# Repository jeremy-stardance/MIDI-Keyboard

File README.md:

## MIDI Keyboard Project

This is for week 3 of Hack Club Half-Life

This is my schematic for eight buttons, run on an Arduino Pro Micro. It should allow me to create an output of notes C through to C.

Here is the PCB design. The wiring is very satisfying.

## Bill Of Materials

| Component | Quantity | Cost ($) |
|---|---:|---:|
| Arduino Pro Micro | 1 | 9.33 |
| Breadboard | 1 | 8.85 |
| Jumper Wire | 130 | 7.92 |

The prices are in $USD. I am using the Arduino Pro Micro as a 'brain' for the project. The wires will be used to jump across my PCB Development Board, and I will use the breadboard to test code and wiring because I am not confident enough in my code to want to just hope for the best.

I already own a PCB Development Board, and 8 Buttons, so didn't need to but them on the BOM.

## What I Have Learnt

Before this, I had only used arduino templates as code, but this is the first time I actually tweaked and changed code. I had to learn a little bit of the coding language (with help from AI). 

Also, I had to learn to find my own schematic files and footprints, rather than have them given to me like in the Starbie project using the tutorial. This took some time.

## Why a MIDI Keyboard

I play piano as a hobby. I thought that a MIDI Keyboard would be a cool devise to be able to have, even though it will not have any sharps or flats.

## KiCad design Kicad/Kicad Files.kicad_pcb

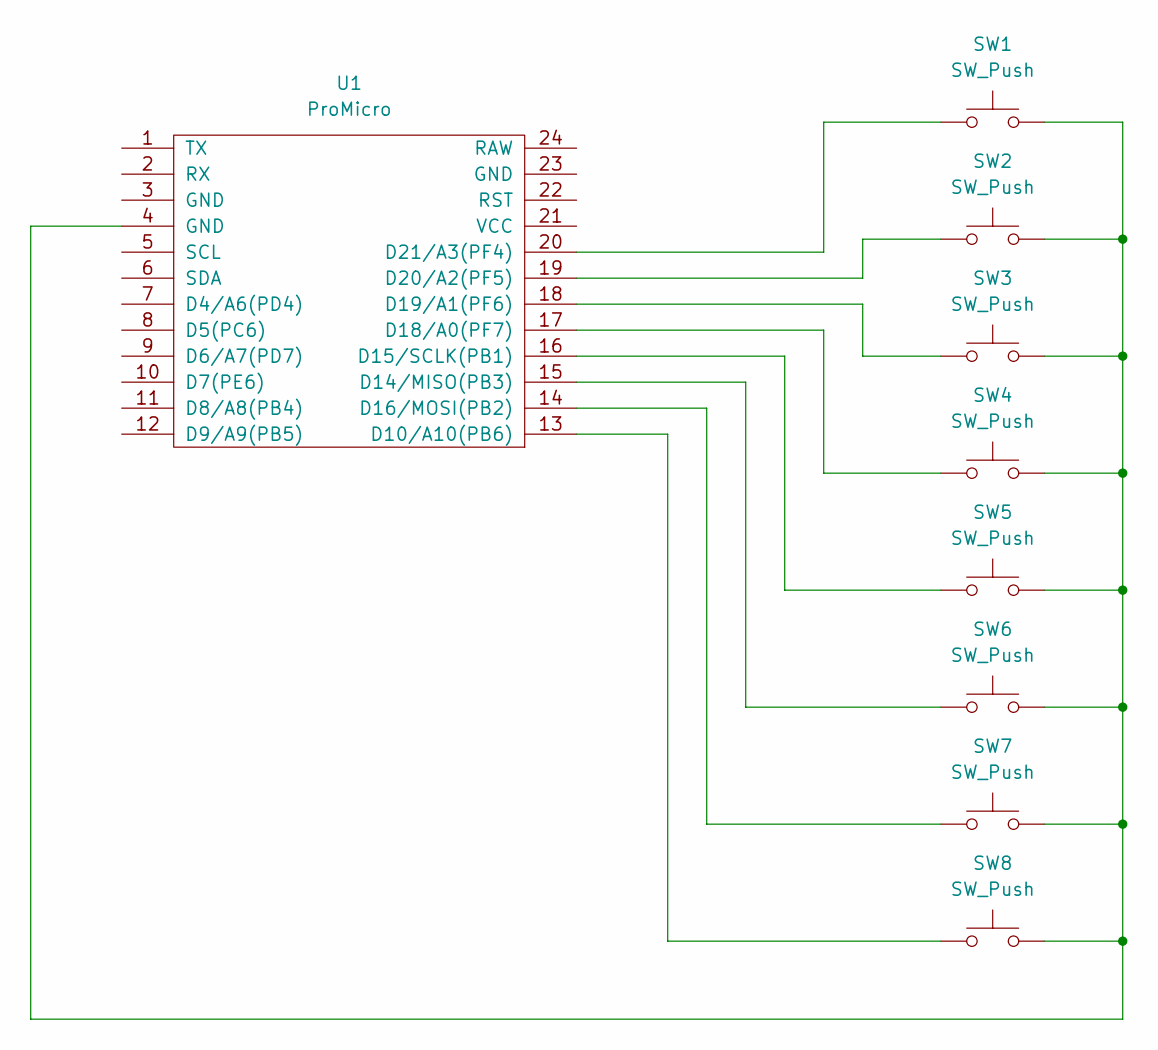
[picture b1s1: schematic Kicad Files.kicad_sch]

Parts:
SW1, SW2, SW3, SW4, SW5, SW6, SW7, SW8: SW_Push; SW_Cherry_MX_1.00u_PCB
U1: ProMicro

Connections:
unnamed: SW1.2, SW2.2, SW3.2, SW4.2, SW5.2, SW6.2, SW7.2, SW8.2, U1.4 (GND)
unnamed: SW8.1, U1.13 (D10/A10(PB6))
unnamed: SW6.1, U1.15 (D14/MISO(PB3))
unnamed: SW5.1, U1.16 (D15/SCLK(PB1))
unnamed: SW7.1, U1.14 (D16/MOSI(PB2))
unnamed: SW4.1, U1.17 (D18/A0(PF7))
unnamed: SW3.1, U1.18 (D19/A1(PF6))
unnamed: SW2.1, U1.19 (D20/A2(PF5))
unnamed: SW1.1, U1.20 (D21/A3(PF4))

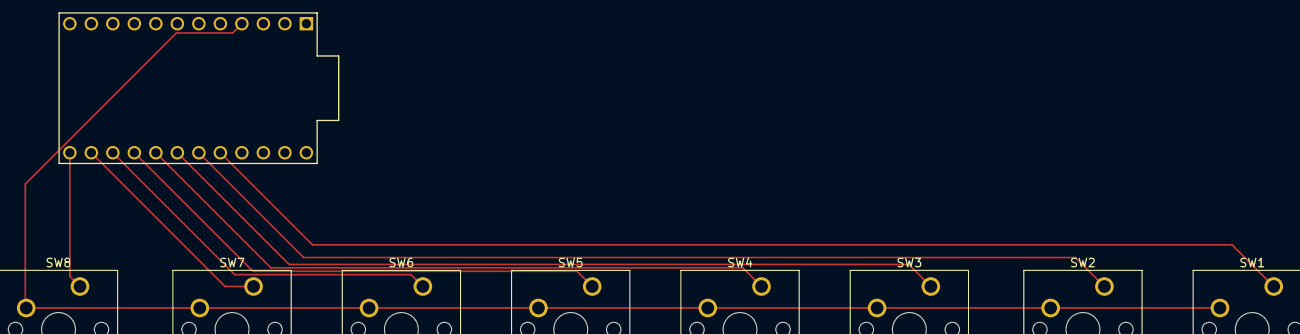
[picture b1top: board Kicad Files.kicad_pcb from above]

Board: 2 copper layers, 9 parts (0 on the bottom side), 9 nets.
